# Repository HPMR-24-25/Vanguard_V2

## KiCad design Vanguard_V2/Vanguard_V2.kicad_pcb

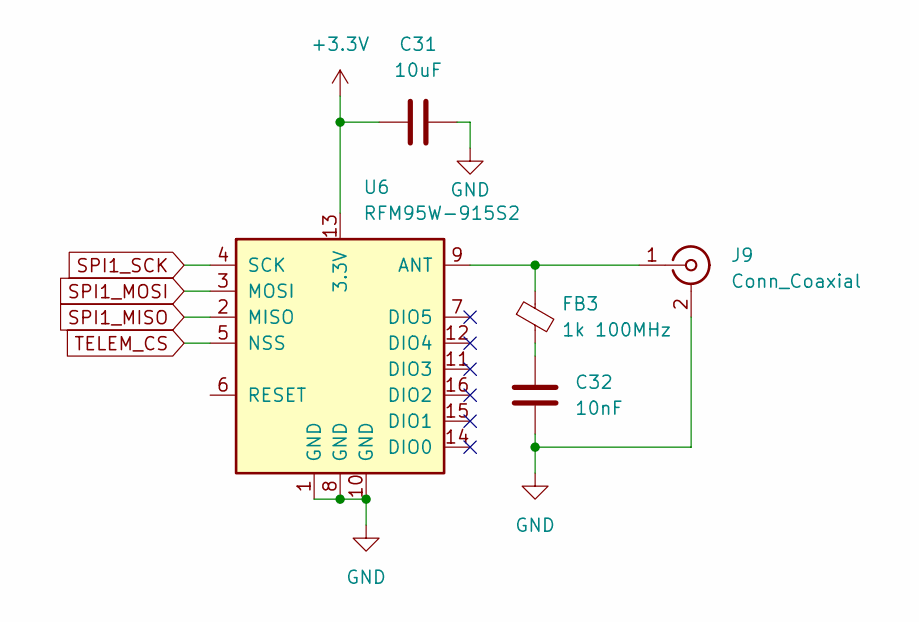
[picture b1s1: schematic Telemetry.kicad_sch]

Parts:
C31: 10uF; C_0402_1005Metric
C32: 10nF; C_0402_1005Metric
FB3: 1k 100MHz; C_0603_1608Metric
J9: Conn_Coaxial; U.FL_Hirose_U.FL-R-SMT-1_Vertical
U6: RFM95W-915S2; HOPERF_RFM9XW_SMD

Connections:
+3.3V: C31.1, U6.13 (3.3V); also elsewhere on the board
GND: C31.2, C32.2, J9.2 (Ext), U6.1 (GND), U6.8 (GND), U6.10 (GND); also elsewhere on the board
unnamed: C32.1, FB3.2
unnamed: FB3.1, J9.1 (In), U6.9 (ANT)
SPI1_MISO: U6.2 (MISO); also elsewhere on the board
SPI1_MOSI: U6.3 (MOSI); also elsewhere on the board
SPI1_SCK: U6.4 (SCK); also elsewhere on the board
TELEM_CS: U6.5 (NSS); also elsewhere on the board

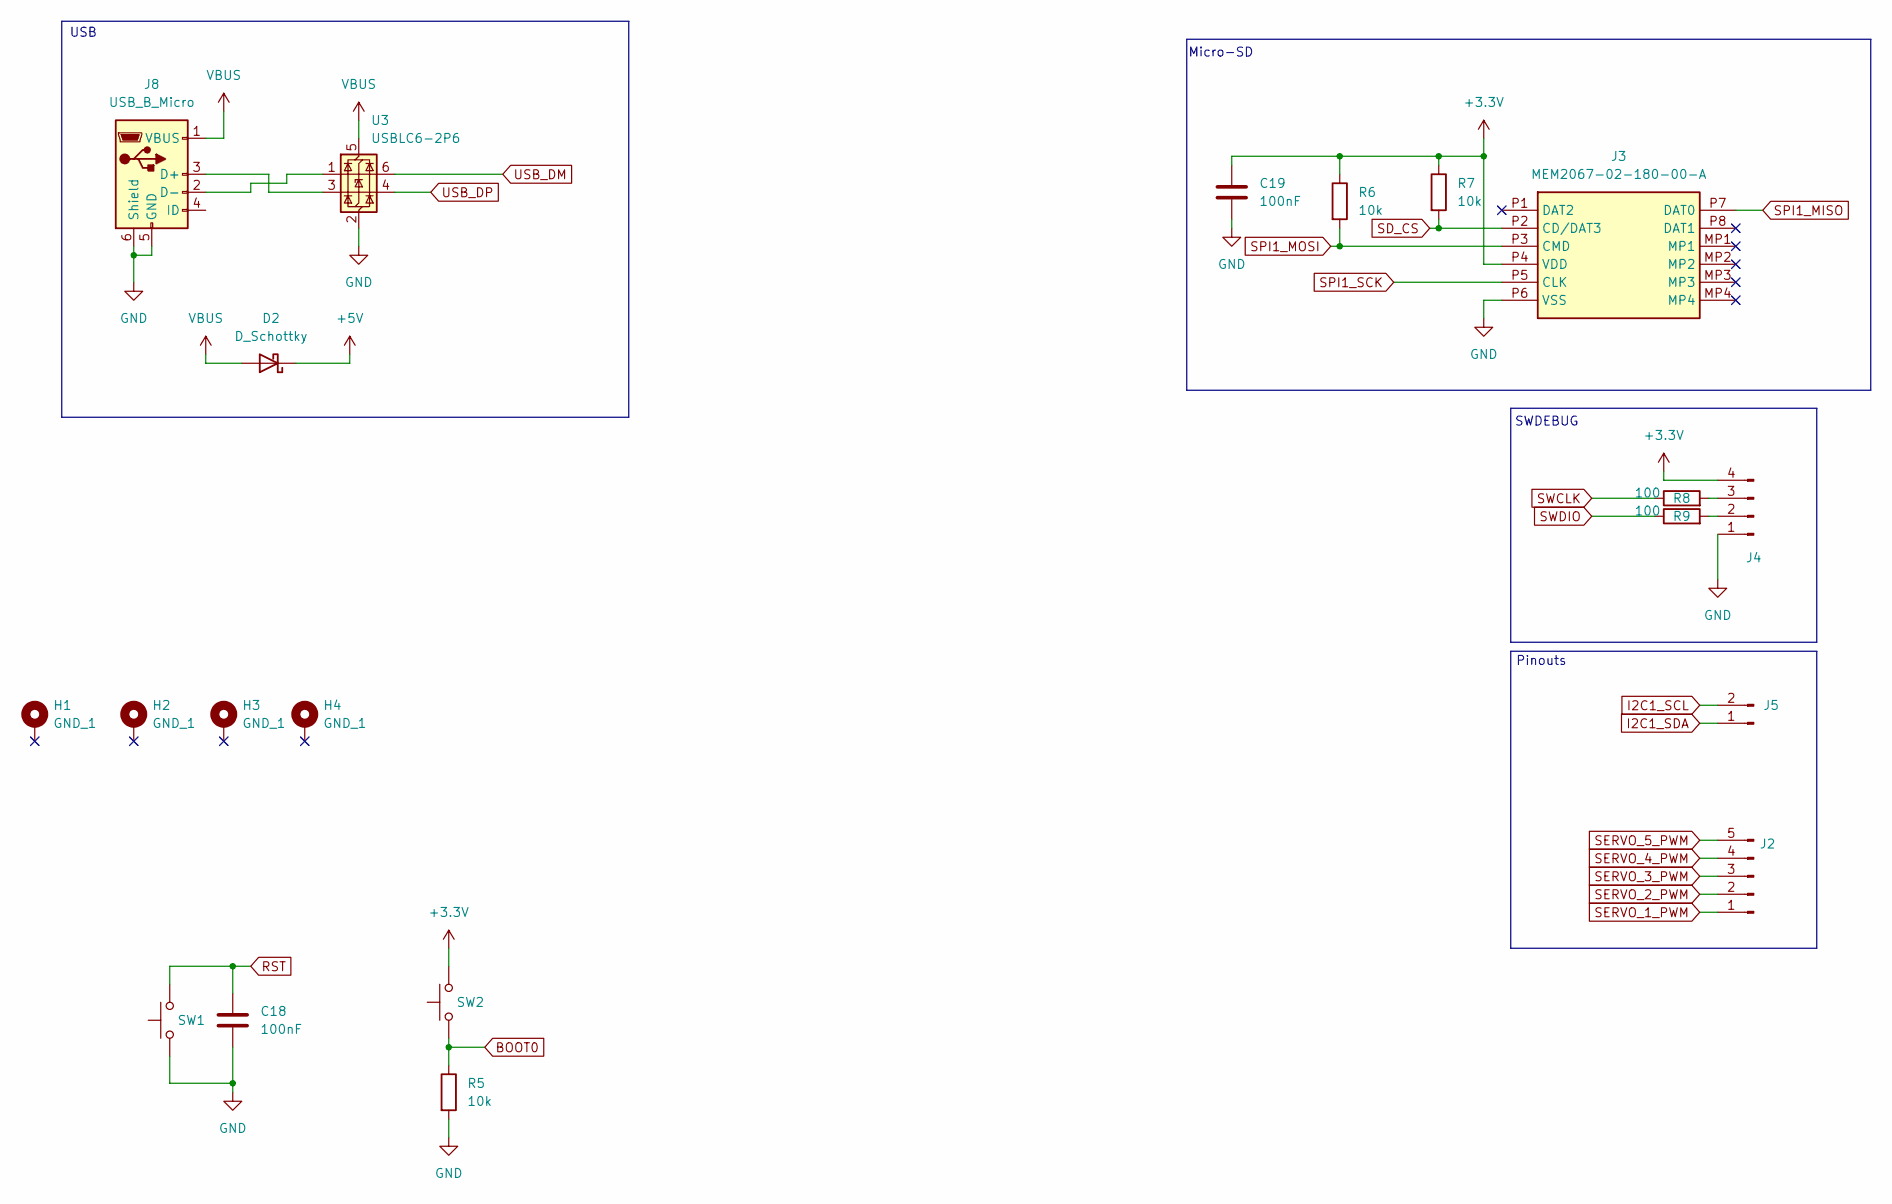
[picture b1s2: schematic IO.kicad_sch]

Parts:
C18, C19: 100nF; C_0402_1005Metric
D2: D_Schottky; D_0402_1005Metric
H1, H2, H3, H4: GND_1; MountingHole_3.2mm_M3
J2: Conn_01x05_Pin; PinHeader_1x05_P2.54mm_Vertical
J3: MEM2067-02-180-00-A; MEM20670218000A; Manufacturer_Part_Number MEM2067-02-180-00-A; Mouser Part Number 640-MEM20670218000A
J4: Conn_01x04_Pin; PinSocket_1x04_P2.54mm_Vertical
J5: Conn_01x02_Pin; PinHeader_1x02_P2.54mm_Vertical
J8: USB_B_Micro; USB_Micro-B_GCT_USB3076-30-A
R5, R6, R7: 10k; R_0402_1005Metric
R8, R9: 100; R_0402_1005Metric
SW1, SW2: SW_Push; SW_SPST_PTS810
U3: USBLC6-2P6; SOT-666

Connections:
+3.3V: C19.1, J3.P4 (VDD), J4.4, R6.1, R7.1, SW2.2; also elsewhere on the board
+5V: D2.1 (K); also elsewhere on the board
BOOT0: R5.1, SW2.1; also elsewhere on the board
GND: C18.2, C19.2, J3.P6 (VSS), J4.1, J8.5 (GND), J8.6 (Shield), R5.2, SW1.1, U3.2 (GND); also elsewhere on the board
I2C1_SCL: J5.2; also elsewhere on the board
I2C1_SDA: J5.1; also elsewhere on the board
unnamed: J4.2, R9.2
unnamed: J4.3, R8.2
unnamed: J8.3 (D+), U3.3 (I/O2)
unnamed: J8.2 (D-), U3.1 (I/O1)
RST: C18.1, SW1.2; also elsewhere on the board
SD_CS: J3.P2 (CD/DAT3), R7.2; also elsewhere on the board
SERVO_1_PWM: J2.1; also elsewhere on the board
SERVO_2_PWM: J2.2; also elsewhere on the board
SERVO_3_PWM: J2.3; also elsewhere on the board
SERVO_4_PWM: J2.4; also elsewhere on the board
SERVO_5_PWM: J2.5; also elsewhere on the board
SPI1_MISO: J3.P7 (DAT0); also elsewhere on the board
SPI1_MOSI: J3.P3 (CMD), R6.2; also elsewhere on the board
SPI1_SCK: J3.P5 (CLK); also elsewhere on the board
SWCLK: R8.1; also elsewhere on the board
SWDIO: R9.1; also elsewhere on the board
USB_DM: U3.6 (I/O1); also elsewhere on the board
USB_DP: U3.4 (I/O2); also elsewhere on the board
VBUS: D2.2 (A), J8.1 (VBUS), U3.5 (VBUS)

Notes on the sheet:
Micro-SD
Pinouts
SWDEBUG
USB

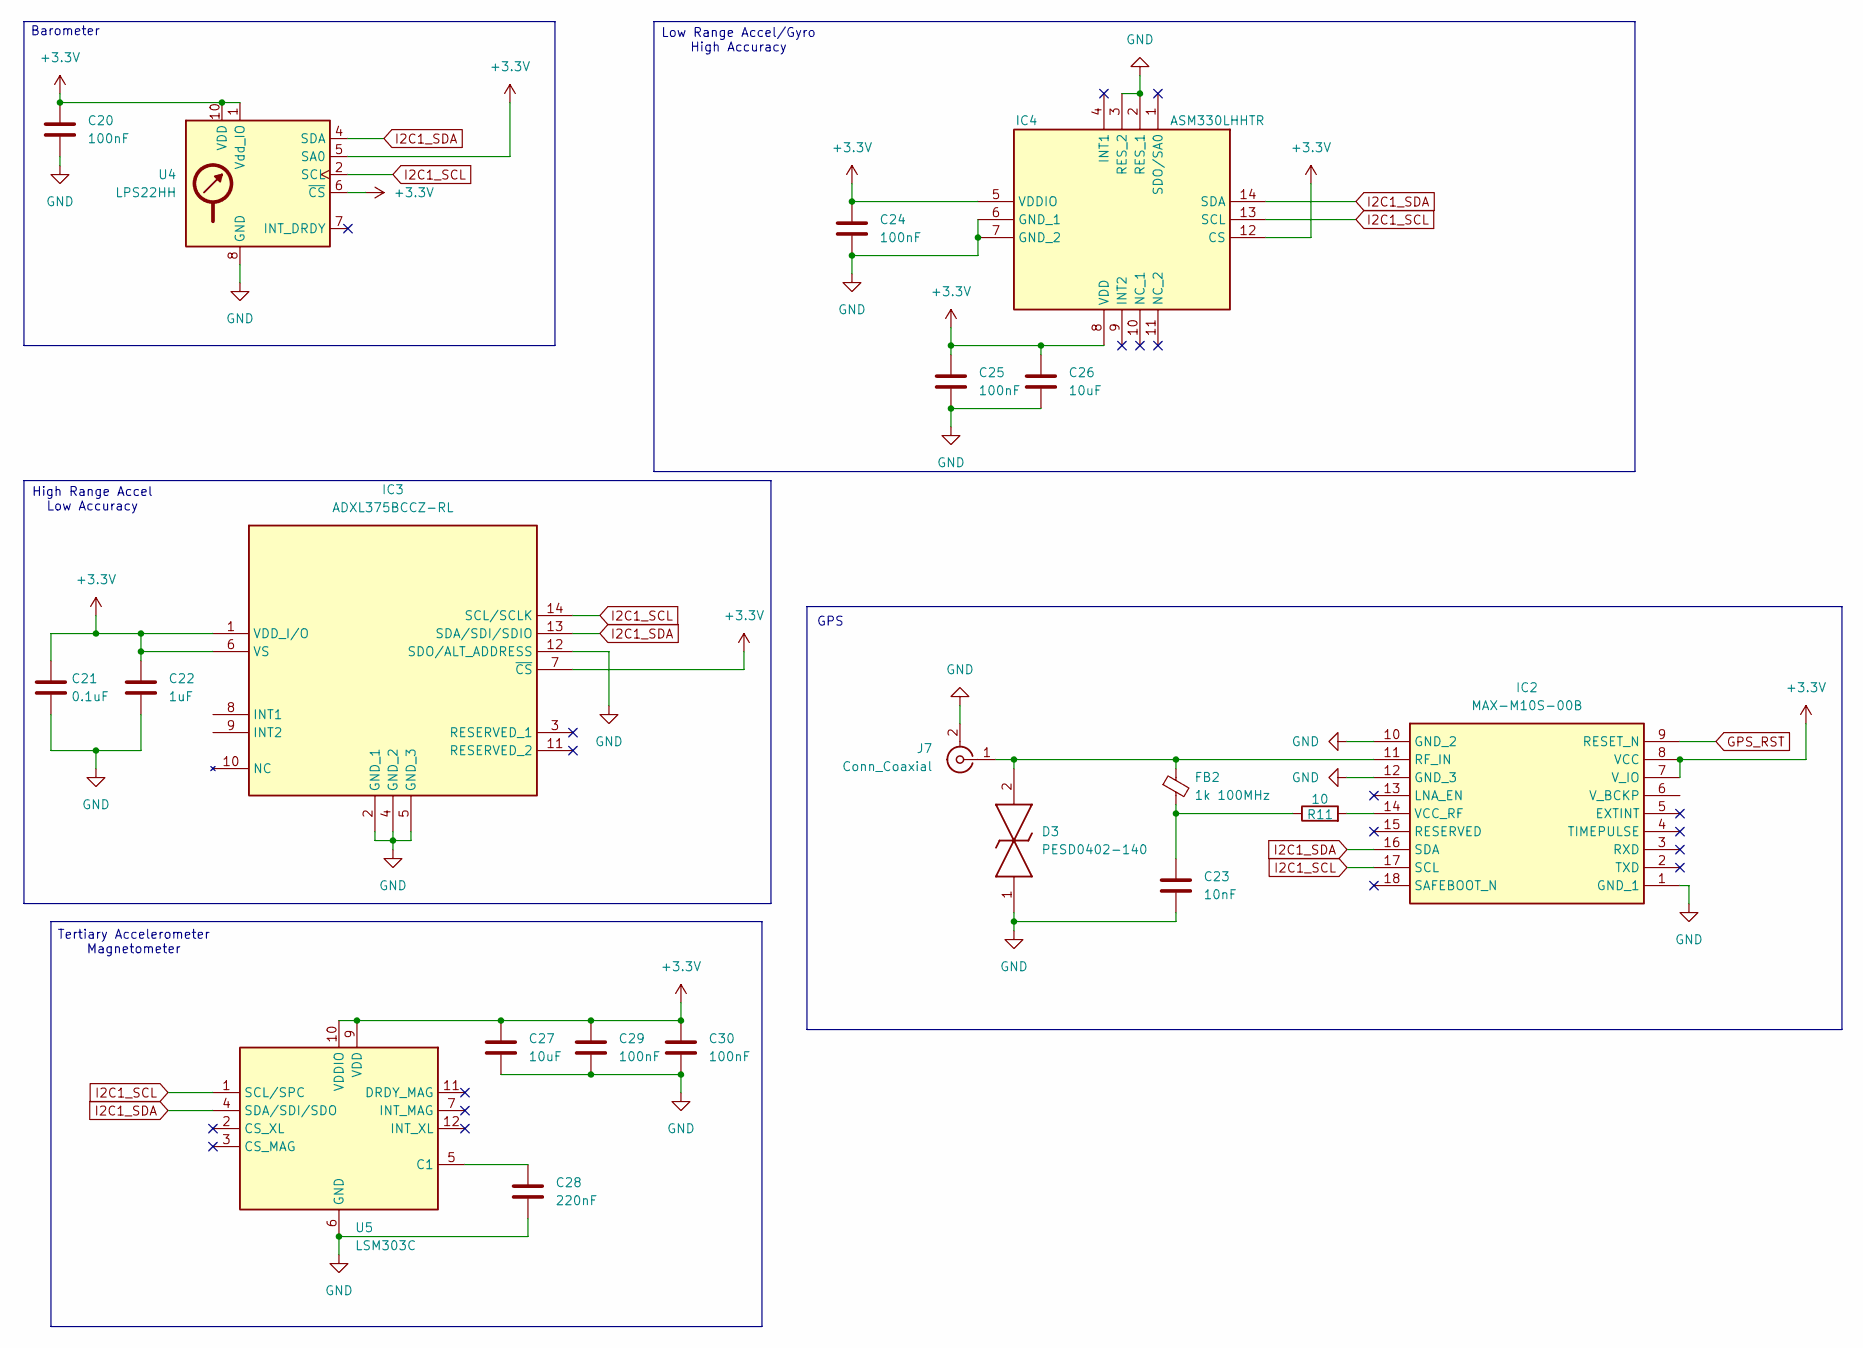
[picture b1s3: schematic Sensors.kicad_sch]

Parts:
C20, C24, C25, C29, C30: 100nF; C_0402_1005Metric
C21: 0.1uF; C_0402_1005Metric
C22: 1uF; C_0402_1005Metric
C23: 10nF; C_0402_1005Metric
C26, C27: 10uF; C_0402_1005Metric
C28: 220nF; C_0402_1005Metric
D3: PESD0402-140; DIONC1005X43N; Mouser Part Number 650-PESD0402-140
FB2: 1k 100MHz; C_0603_1608Metric
IC2: MAX-M10S-00B; MAXM10S00B; Mouser Part Number 377-MAX-M10S-00B
IC3: ADXL375BCCZ-RL; ADXL375BCCZRL; Manufacturer_Part_Number ADXL375BCCZ-RL; Mouser Part Number 584-ADXL375BCCZ-RL
IC4: ASM330LHHTR; LSM6DS3USTR; Manufacturer_Part_Number ASM330LHHTR; Mouser Part Number 511-ASM330LHHTR
J7: Conn_Coaxial; U.FL_Hirose_U.FL-R-SMT-1_Vertical
R11: 10; R_0402_1005Metric
U4: LPS22HH; ST_HLGA-10_2x2mm_P0.5mm_LayoutBorder3x2y
U5: LSM303C; LGA-12_2x2mm_P0.5mm

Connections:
+3.3V: C20.1, C21.1, C22.1, C24.1, C25.1, C26.1, C27.1, C29.1, C30.1, IC2.7 (V_IO), IC2.8 (VCC), IC3.1 (VDD_I/O), IC3.6 (VS), IC3.7 (~CS), IC4.5 (VDDIO), IC4.8 (VDD), IC4.12 (CS), U4.1 (Vdd_IO), U4.5 (SA0), U4.6 (~CS), U4.10 (VDD), U5.9 (VDD), U5.10 (VDDIO); also elsewhere on the board
GND: C20.2, C21.2, C22.2, C23.2, C24.2, C25.2, C26.2, C27.2, C28.2, C29.2, C30.2, D3.1, IC2.1 (GND_1), IC2.10 (GND_2), IC2.12 (GND_3), IC3.2 (GND_1), IC3.4 (GND_2), IC3.5 (GND_3), IC3.12 (SDO/ALT_ADDRESS), IC4.2 (RES_1), IC4.3 (RES_2), IC4.6 (GND_1), IC4.7 (GND_2), J7.2 (Ext), U4.3 (GND), U4.8 (GND), U4.9 (GND), U5.6 (GND), U5.8 (GND); also elsewhere on the board
GPS_RST: IC2.9 (RESET_N)
I2C1_SCL: IC2.17 (SCL), IC3.14 (SCL/SCLK), IC4.13 (SCL), U4.2 (SCL), U5.1 (SCL/SPC); also elsewhere on the board
I2C1_SDA: IC2.16 (SDA), IC3.13 (SDA/SDI/SDIO), IC4.14 (SDA), U4.4 (SDA), U5.4 (SDA/SDI/SDO); also elsewhere on the board
unnamed: C23.1, FB2.2, R11.1
unnamed: D3.2, FB2.1, IC2.11 (RF_IN), J7.1 (In)
unnamed: IC2.14 (VCC_RF), R11.2
unnamed: C28.1, U5.5 (C1)

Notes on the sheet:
GPS
Barometer
High Range Accel Low Accuracy
Tertiary Accelerometer Magnetometer
Low Range Accel/Gyro High Accuracy

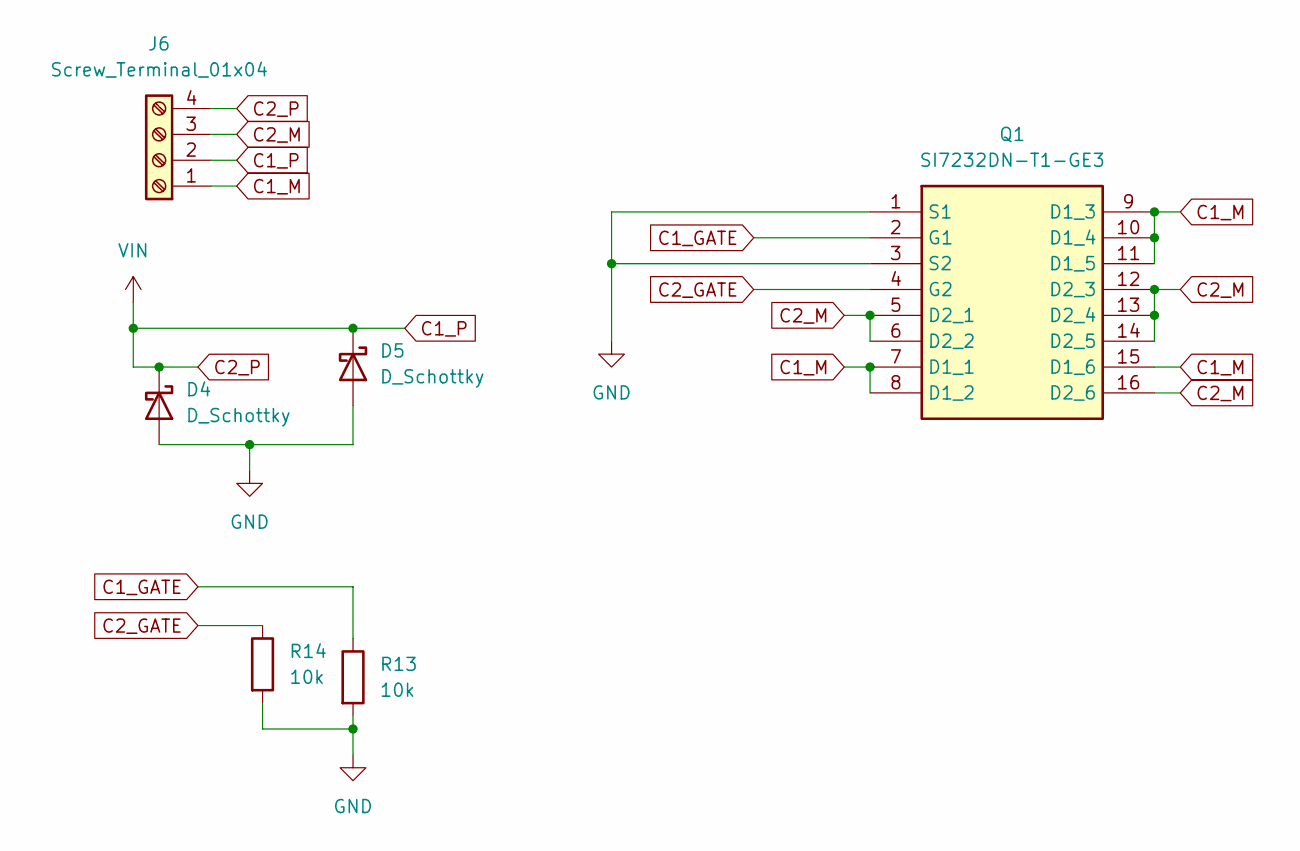
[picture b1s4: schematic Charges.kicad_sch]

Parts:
D4, D5: D_Schottky; D_0603_1608Metric
J6: Screw_Terminal_01x04; TerminalBlock_Xinya_XY308-2.54-4P_1x04_P2.54mm_Horizontal
Q1: SI7232DN-T1-GE3; SI7232DNT1GE3; Mouser Part Number 781-SI7232DN-GE3
R13, R14: 10k; R_0402_1005Metric

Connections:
C1_GATE: Q1.2 (G1), R13.1; also elsewhere on the board
C1_M: J6.1, Q1.7 (D1_1), Q1.8 (D1_2), Q1.9 (D1_3), Q1.10 (D1_4), Q1.11 (D1_5), Q1.15 (D1_6)
C1_P: D4.1 (K), D5.1 (K), J6.2, J6.4; also elsewhere on the board
C2_GATE: Q1.4 (G2), R14.1; also elsewhere on the board
C2_M: J6.3, Q1.5 (D2_1), Q1.6 (D2_2), Q1.12 (D2_3), Q1.13 (D2_4), Q1.14 (D2_5), Q1.16 (D2_6)
GND: D4.2 (A), D5.2 (A), Q1.1 (S1), Q1.3 (S2), R13.2, R14.2; also elsewhere on the board

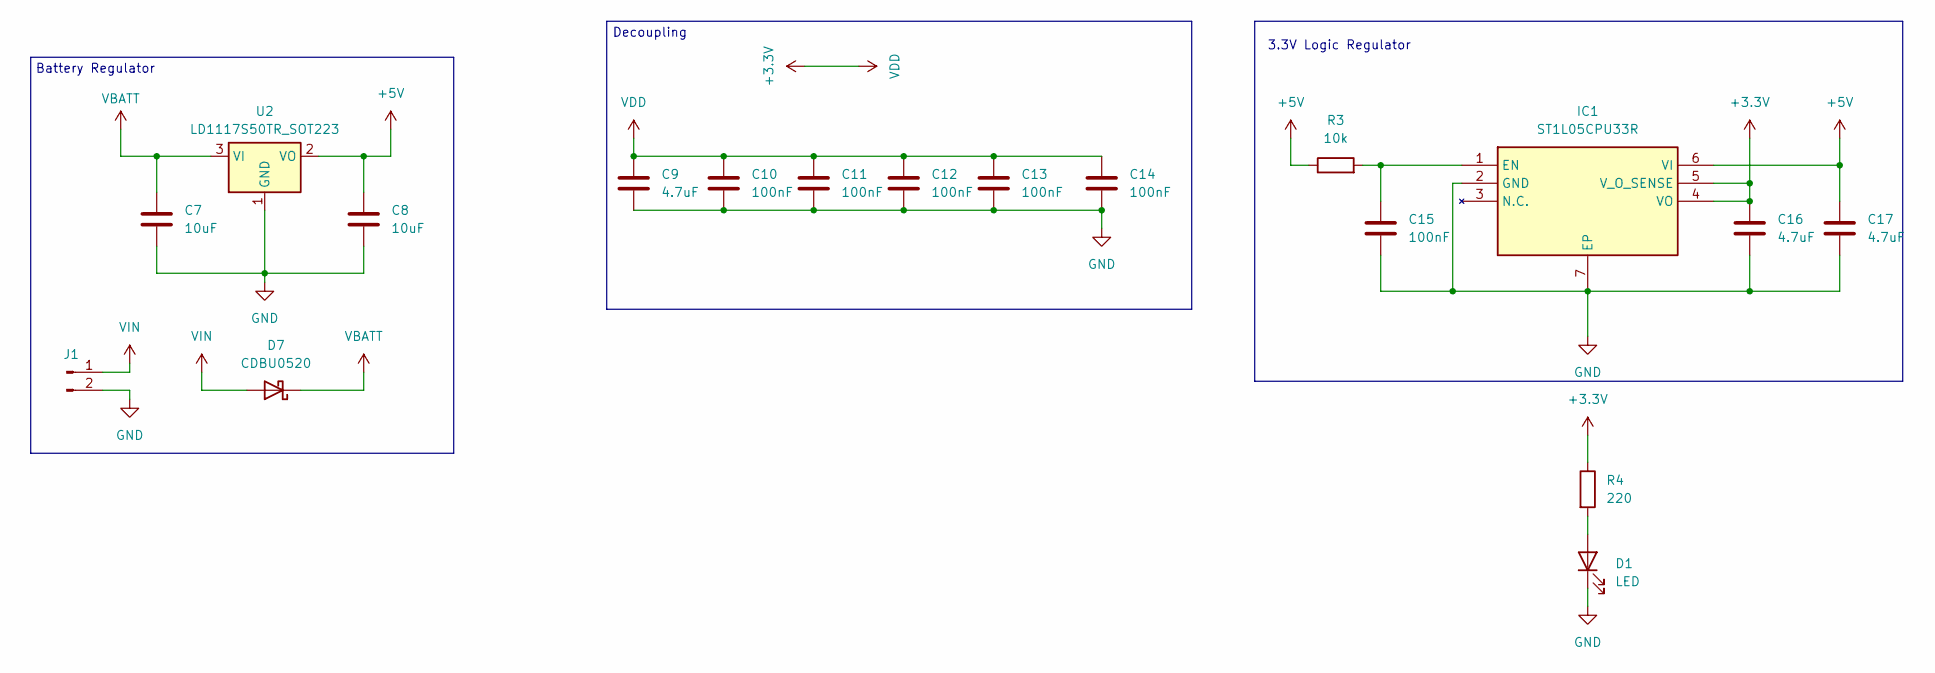
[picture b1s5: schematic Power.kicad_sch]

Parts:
C7, C8: 10uF; C_0402_1005Metric
C9, C16, C17: 4.7uF; C_0402_1005Metric
C10, C11, C12, C13, C14, C15: 100nF; C_0402_1005Metric
D1: LED; LED_0603_1608Metric
D7: CDBU0520; R_0402_1005Metric; MPN CDBU0520
IC1: ST1L05CPU33R; SON95P300X300X100-7N-D; Manufacturer_Part_Number ST1L05CPU33R; Mouser Part Number 511-ST1L05CPU33R
J1: Conn_01x02_Pin; PinHeader_1x02_P2.54mm_Vertical
R3: 10k; R_0402_1005Metric
R4: 220; R_0402_1005Metric
U2: LD1117S50TR_SOT223; SOT-223-3_TabPin2

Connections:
+3.3V: C9.1, C10.1, C11.1, C12.1, C13.1, C14.1, C16.1, IC1.4 (VO), IC1.5 (V_O_SENSE), R4.1; also elsewhere on the board
+5V: C8.1, C17.1, IC1.6 (VI), R3.1, U2.2 (VO); also elsewhere on the board
C1_P: D7.2 (A), J1.1; also elsewhere on the board
GND: C7.2, C8.2, C9.2, C10.2, C11.2, C12.2, C13.2, C14.2, C15.2, C16.2, C17.2, D1.1 (K), IC1.2 (GND), IC1.7 (EP), J1.2, U2.1 (GND); also elsewhere on the board
unnamed: D1.2 (A), R4.2
unnamed: C15.1, IC1.1 (EN), R3.2
VBATT: C7.1, D7.1 (K), U2.3 (VI)

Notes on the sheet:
Decoupling
Battery Regulator
3.3V Logic Regulator

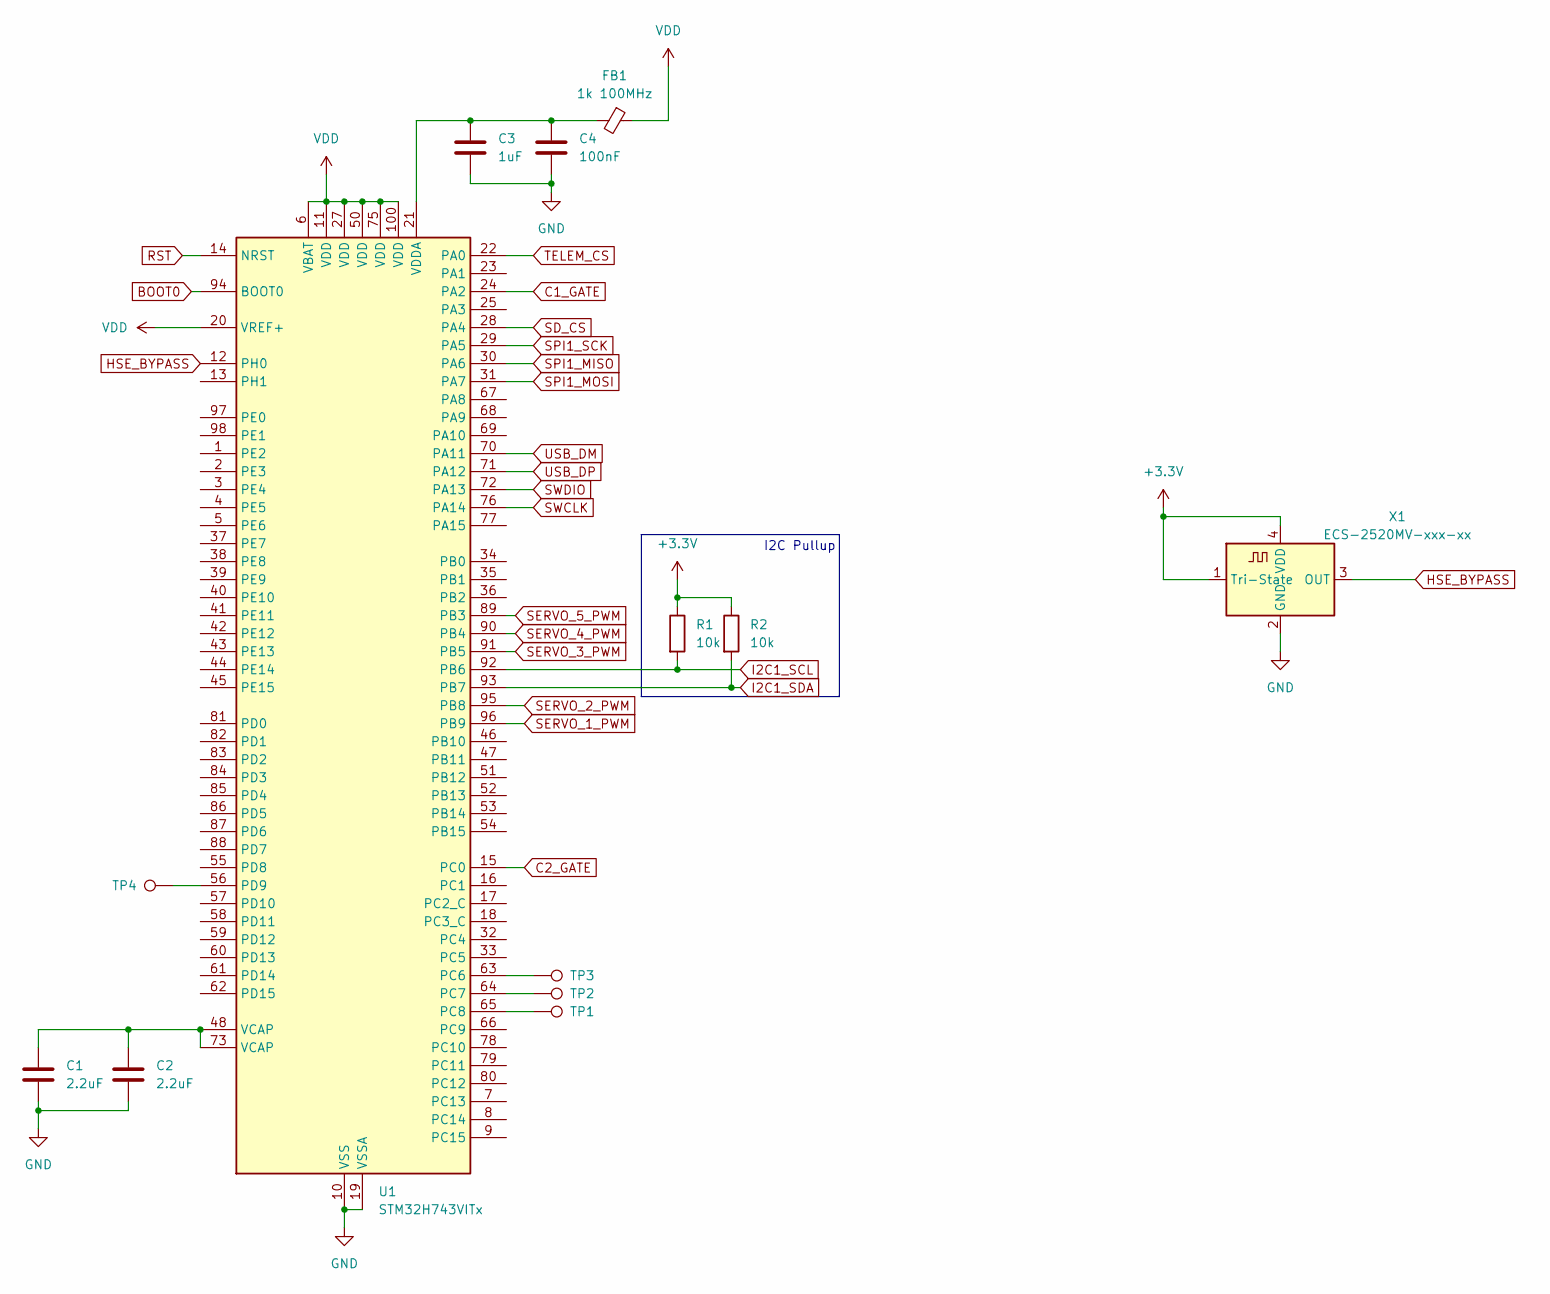
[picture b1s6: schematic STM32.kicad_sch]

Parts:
C1, C2: 2.2uF; C_0402_1005Metric
C3: 1uF; C_0402_1005Metric
C4: 100nF; C_0402_1005Metric
FB1: 1k 100MHz; C_0603_1608Metric
R1, R2: 10k; R_0402_1005Metric
TP1, TP2, TP3, TP4: TestPoint; SolderWirePad_1x01_SMD_1x2mm
U1: STM32H743VITx; LQFP-100_14x14mm_P0.5mm
X1: ECS-2520MV-xxx-xx; Oscillator_SMD_ECS_2520MV-xxx-xx-4Pin_2.5x2.0mm

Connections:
+3.3V: FB1.1, R1.1, R2.1, U1.6 (VBAT), U1.11 (VDD), U1.20 (VREF+), U1.27 (VDD), U1.50 (VDD), U1.75 (VDD), U1.100 (VDD), X1.1 (Tri-State), X1.4 (VDD); also elsewhere on the board
BOOT0: U1.94 (BOOT0); also elsewhere on the board
C1_GATE: U1.24 (PA2); also elsewhere on the board
C2_GATE: U1.15 (PC0); also elsewhere on the board
GND: C1.2, C2.2, C3.2, C4.2, U1.10 (VSS), U1.19 (VSSA), U1.26 (VSS), U1.49 (VSS), U1.74 (VSS), U1.99 (VSS), X1.2 (GND); also elsewhere on the board
HSE_BYPASS: U1.12 (PH0), X1.3 (OUT)
I2C1_SCL: R1.2, U1.92 (PB6); also elsewhere on the board
I2C1_SDA: R2.2, U1.93 (PB7); also elsewhere on the board
unnamed: C1.1, C2.1, U1.48 (VCAP), U1.73 (VCAP)
unnamed: TP3.1, U1.63 (PC6)
unnamed: TP2.1, U1.64 (PC7)
unnamed: TP1.1, U1.65 (PC8)
unnamed: TP4.1, U1.56 (PD9)
unnamed: C3.1, C4.1, FB1.2, U1.21 (VDDA)
RST: U1.14 (NRST); also elsewhere on the board
SD_CS: U1.28 (PA4); also elsewhere on the board
SERVO_1_PWM: U1.96 (PB9); also elsewhere on the board
SERVO_2_PWM: U1.95 (PB8); also elsewhere on the board
SERVO_3_PWM: U1.91 (PB5); also elsewhere on the board
SERVO_4_PWM: U1.90 (PB4); also elsewhere on the board
SERVO_5_PWM: U1.89 (PB3); also elsewhere on the board
SPI1_MISO: U1.30 (PA6); also elsewhere on the board
SPI1_MOSI: U1.31 (PA7); also elsewhere on the board
SPI1_SCK: U1.29 (PA5); also elsewhere on the board
SWCLK: U1.76 (PA14); also elsewhere on the board
SWDIO: U1.72 (PA13); also elsewhere on the board
TELEM_CS: U1.22 (PA0); also elsewhere on the board
USB_DM: U1.70 (PA11); also elsewhere on the board
USB_DP: U1.71 (PA12); also elsewhere on the board

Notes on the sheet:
I2C Pullup

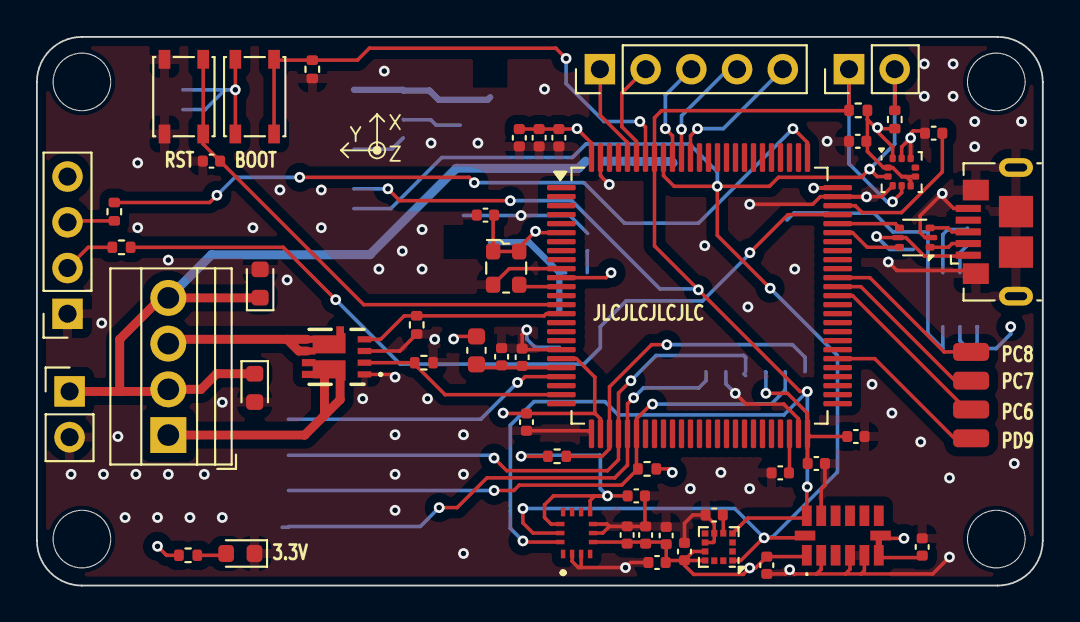
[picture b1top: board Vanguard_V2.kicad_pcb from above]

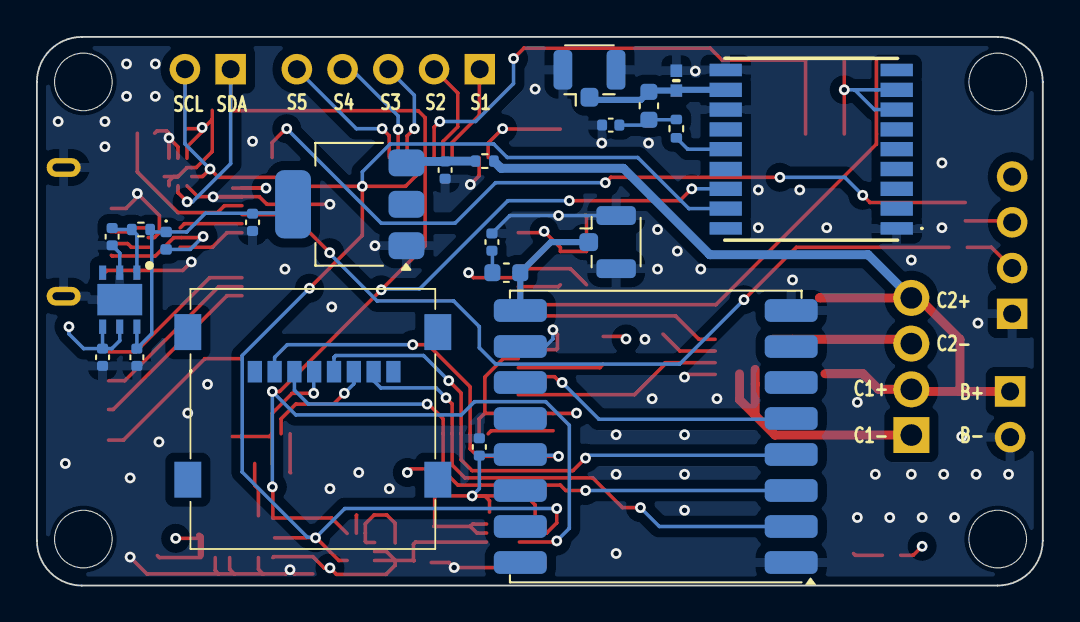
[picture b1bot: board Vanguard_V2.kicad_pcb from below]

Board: 4 copper layers, 55.9 x 30.5 mm, 82 parts (22 on the bottom side), 47 nets.

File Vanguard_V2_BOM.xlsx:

Reference | Value | Datasheet | Footprint | Qty
C1,C2 | 2.2uF | ~ | Capacitor_SMD:C_0402_1005Metric | 2
C3,C22 | 1uF | ~ | Capacitor_SMD:C_0402_1005Metric | 2
C7,C8,C26,C27,C31 | 10uF | ~ | Capacitor_SMD:C_0402_1005Metric | 5
C9,C16,C17 | 4.7uF | ~ | Capacitor_SMD:C_0402_1005Metric | 3
C4,C10,C11,C12,C13,C14,C15,C18,C19,C20,C21,C24,C25,C29,C30 | 0.1uF | ~ | Capacitor_SMD:C_0402_1005Metric | 15
C23,C32 | 10nF | ~ | Capacitor_SMD:C_0402_1005Metric | 2
C28 | 220nF | ~ | Capacitor_SMD:C_0402_1005Metric | 1
D1 | LED | ~ | LED_SMD:LED_0603_1608Metric | 1
D2 | D_Schottky | ~ | Diode_SMD:D_0402_1005Metric | 1
D3 | PESD0402-140 | https://www.littelfuse.com/~/media/electronics/product_speci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 | VanguardLib:DIONC1005X43N | 1
D4,D5 | D_Schottky | ~ | Diode_SMD:D_0603_1608Metric | 2
FB1,FB2,FB3 | 1k 100MHz | https://www.mouser.com/datasheet/2/281/ENFA0004-1915711.pdf | Capacitor_SMD:C_0603_1608Metric | 3
IC1 | ST1L05CPU33R | https://www.mouser.de/datasheet/2/389/st1l05-974244.pdf | VanguardLib:SON95P300X300X100-7N-D | 1
IC2 | MAX-M10S-00B | https://content.u-blox.com/sites/default/files/MAX-M10S_Inte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 | VanguardLib:MAXM10S00B | 1
IC3 | ADXL375BCCZ-RL | https://www.analog.com/media/en/technical-documentation/data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 | ADXL375BCCZRL | 1
IC4 | ASM330LHHTR | https://www.st.com/resource/en/datasheet/asm330lhh.pdf | VanguardLib:LSM6DS3USTR | 1
J1,J5 | Conn_01x02_Pin | ~ | Connector_PinHeader_2.54mm:PinHeader_1x02_P2.54mm_Vertical | 2
J2 | Conn_01x05_Pin | ~ | Connector_PinHeader_2.54mm:PinHeader_1x05_P2.54mm_Vertical | 1
J3 | MEM2067-02-180-00-A | https://gct.co/files/drawings/mem2067.pdf | VanguardLib:MEM20670218000A | 1
J4 | Conn_01x04_Pin | ~ | Connector_PinSocket_2.54mm:PinSocket_1x04_P2.54mm_Vertical | 1
J6 | Screw_Terminal_01x04 | ~ | TerminalBlock:TerminalBlock_Xinya_XY308-2.54-4P_1x04_P2.54mm_Horizontal | 1
J7,J9 | Conn_Coaxial | ~ | Connector_Coaxial:U.FL_Hirose_U.FL-R-SMT-1_Vertical | 2
J8 | USB_B_Micro | ~ | Connector_USB:USB_Micro-B_GCT_USB3076-30-A | 1
Q1 | SI7232DN-T1-GE3 | https://www.vishay.com/docs/68986/si7232dn.pdf | SI7232DNT1GE3 | 1
R1,R2,R3,R5,R6,R7,R13,R14 | 10k | ~ | Resistor_SMD:R_0402_1005Metric | 8
R4 | 220 | ~ | Resistor_SMD:R_0402_1005Metric | 1
R8,R9 | 100 | ~ | Resistor_SMD:R_0402_1005Metric | 2
R11 | 10 | ~ | Resistor_SMD:R_0402_1005Metric | 1
SW1,SW2 | SW_Push | ~ | Button_Switch_SMD:SW_SPST_PTS810 | 2
TP1,TP2,TP3,TP4 | TestPoint | ~ | Connector_Wire:SolderWirePad_1x01_SMD_1x2mm | 4
U1 | STM32H743VITx | https://www.st.com/resource/en/datasheet/stm32h743vi.pdf | Package_QFP:LQFP-100_14x14mm_P0.5mm | 1
U2 | LD1117S50TR_SOT223 | http://www.st.com/st-web-ui/static/active/en/resource/techni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 | Package_TO_SOT_SMD:SOT-223-3_TabPin2 | 1
U3 | USBLC6-2P6 | https://www.st.com/resource/en/datasheet/usblc6-2.pdf | Package_TO_SOT_SMD:SOT-666 | 1
U4 | LPS22HH | https://www.st.com/resource/en/datasheet/lps22hh.pdf | Package_LGA:ST_HLGA-10_2x2mm_P0.5mm_LayoutBorder3x2y | 1
U5 | LSM303C | www.st.com/resource/en/datasheet/lsm303c.pdf | Package_LGA:LGA-12_2x2mm_P0.5mm | 1
U6 | RFM95W-915S2 | https://www.hoperf.com/data/upload/portal/20181127/5bfcbea20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 | RF_Module:HOPERF_RFM9XW_SMD | 1
X1 | ECS-2520MV-xxx-xx | https://www.ecsxtal.com/store/pdf/ECS-2520MV.pdf | Oscillator:Oscillator_SMD_ECS_2520MV-xxx-xx-4Pin_2.5x2.0mm | 1

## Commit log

2024-11-26 Added pcb
2024-12-01 V2 Board Ready
2024-12-01 started layout for V2.1
2024-12-03 Begun board routing
2024-12-03 Everything is placed
2024-12-03 Removed locks
2025-01-26 Added ejection charges
2025-02-03 Finalized board
2025-03-08 Fixed sensors
2025-03-08 added more silkscreen
